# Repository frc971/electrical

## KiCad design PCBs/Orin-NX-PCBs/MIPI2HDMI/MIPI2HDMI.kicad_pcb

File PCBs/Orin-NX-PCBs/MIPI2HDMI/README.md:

Step file is made for mm and has .01mm accuracy.

Last Revision made on Nov 17 2023

For questions regarding the pcb or schematic contact Alex Lenkov or Scott Berman

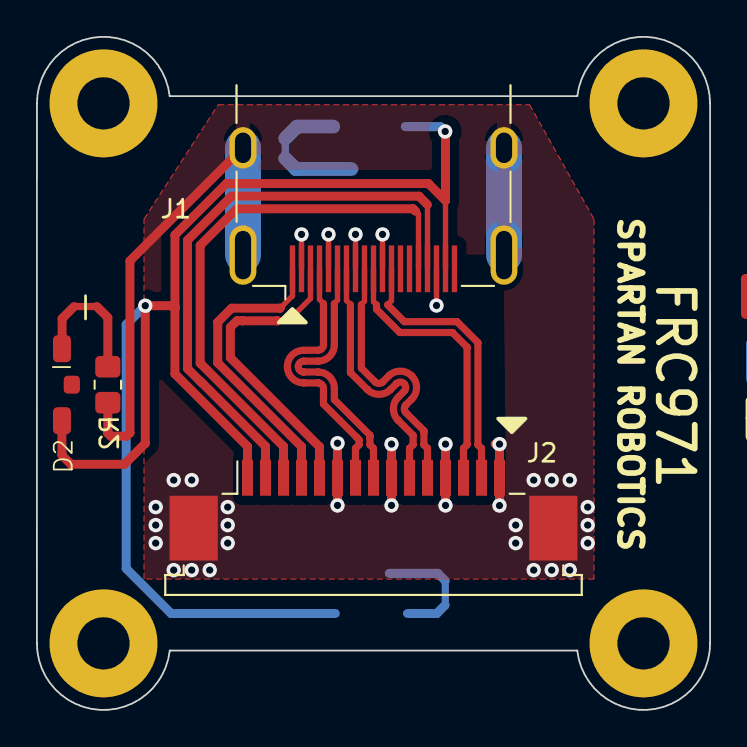
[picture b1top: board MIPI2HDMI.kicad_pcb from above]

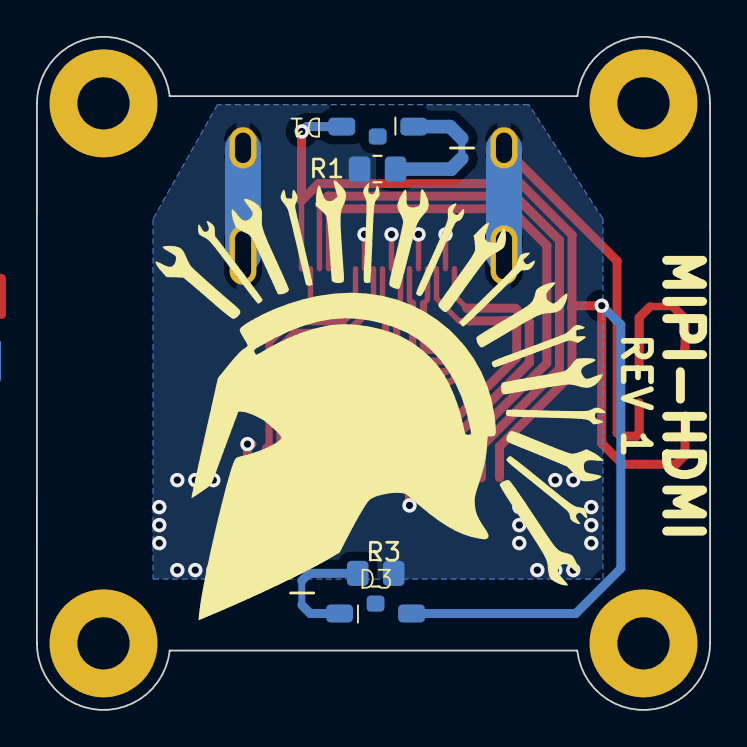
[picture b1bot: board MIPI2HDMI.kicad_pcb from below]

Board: 2 copper layers, 37.4 x 37.4 mm, 12 parts (4 on the bottom side), 15 nets.

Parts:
D1, D2, D3: LED; SM1204PGC
H1, H2, H3, H4: M2.5 Mounting Hole; MountingHole_2.7mm_Pad
J1: HDMI; HDMI_A_Molex_208658-1001_Horizontal
J2: 1-84953-5; TE_1-84953-5_1x15-1MP_P1.0mm_Horizontal
R1, R2, R3: 60; R_0805_2012Metric_Pad1.20x1.40mm_HandSolder

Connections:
+3V3: D1.1 (A), D2.1 (A), D3.1 (A), J1.18 (+5V), J2.15
/CAM_CK_N: J1.6 (D1-), J2.8
/CAM_CK_P: J1.4 (D1+), J2.9
/CAM_D0_N: J1.12 (CK-), J2.2
/CAM_D0_P: J1.10 (CK+), J2.3
/CAM_D1_N: J1.9 (D0-), J2.5
/CAM_D1_P: J1.7 (D0+), J2.6
/CAM_MCLK: J1.1 (D2+), J2.12
/CAM_SCL: J1.15 (SCL), J2.13
/CAM_SDA: J1.16 (SDA), J2.14
/PWR_DN_LS: J1.3 (D2-), J2.11
GND: J1.2 (D2S), J1.5 (D1S), J1.8 (D0S), J1.11 (CKS), J1.17 (GND), J1.SH, J2.1, J2.4, J2.7, J2.10, J2.16, J2.17, R1.2, R2.2, R3.2
unnamed: D1.2 (K), R1.1
unnamed: D2.2 (K), R2.1
unnamed: D3.2 (K), R3.1

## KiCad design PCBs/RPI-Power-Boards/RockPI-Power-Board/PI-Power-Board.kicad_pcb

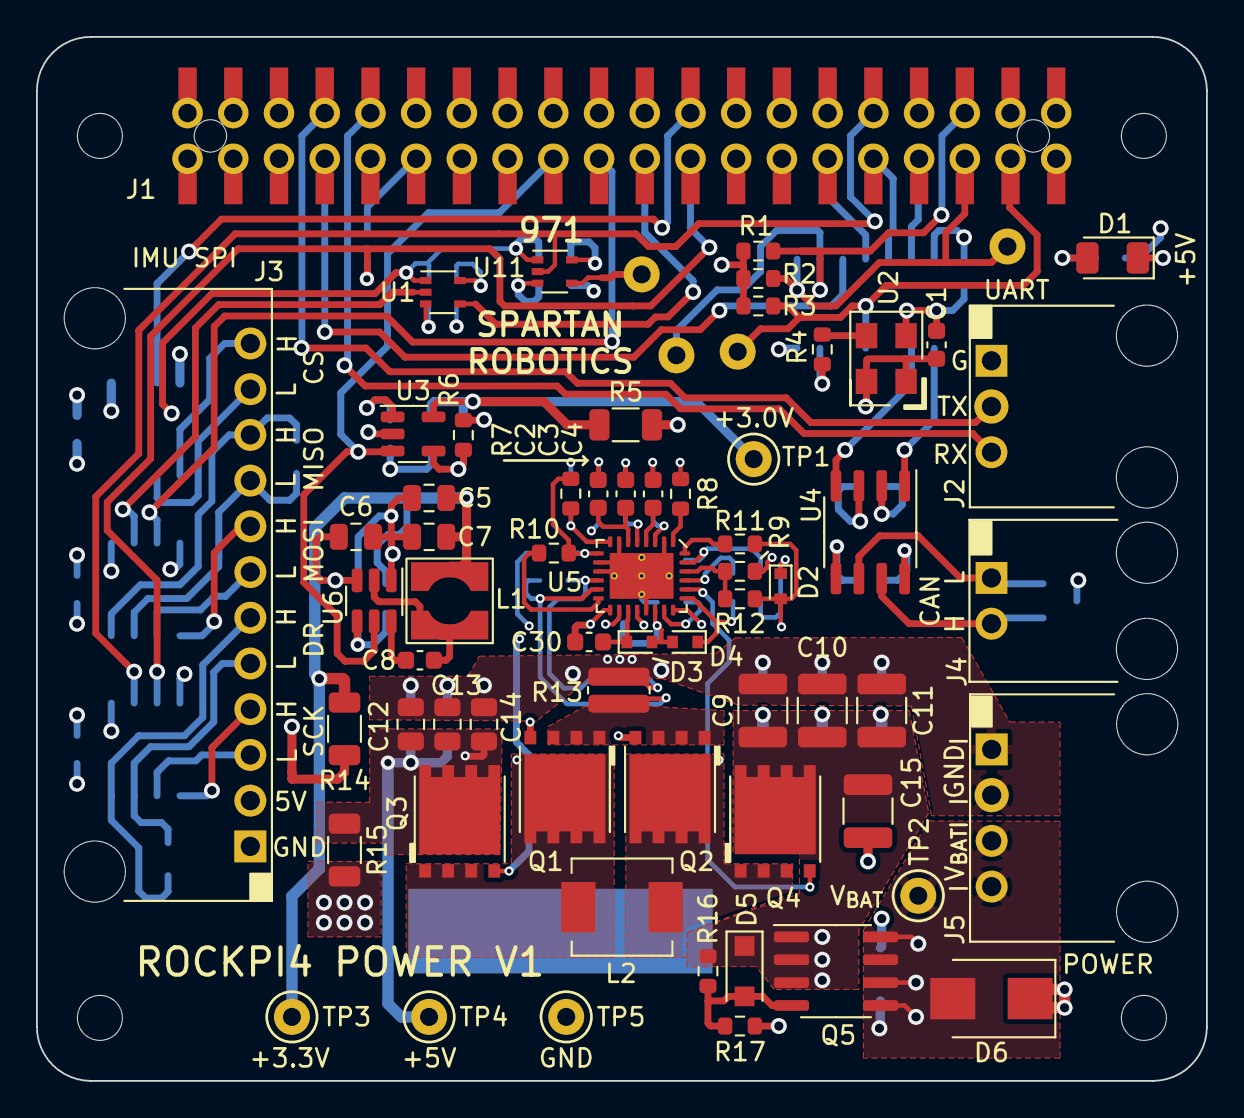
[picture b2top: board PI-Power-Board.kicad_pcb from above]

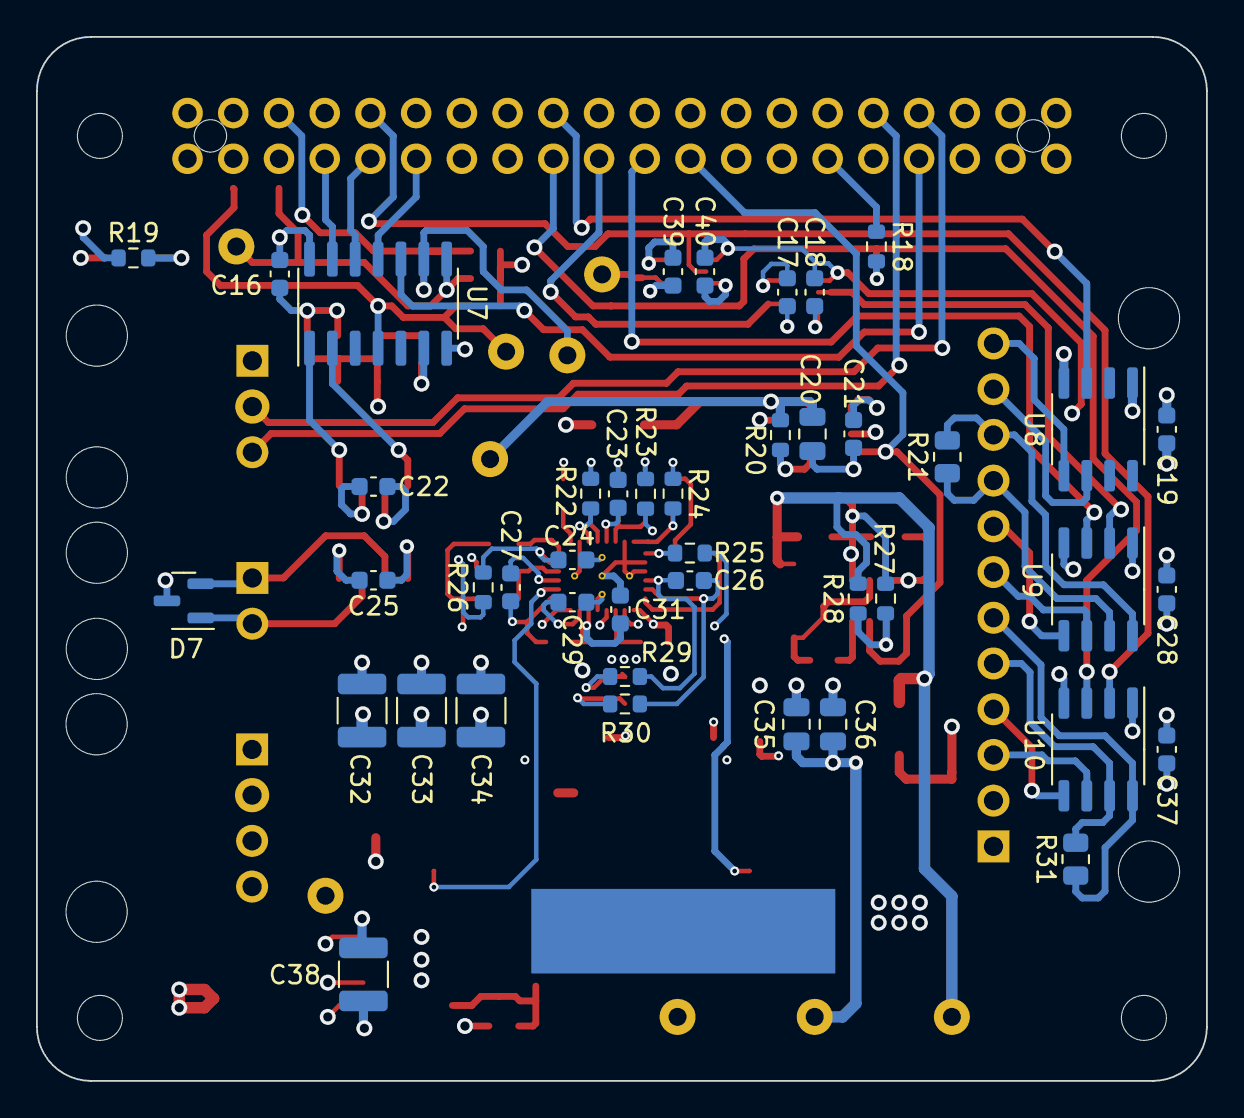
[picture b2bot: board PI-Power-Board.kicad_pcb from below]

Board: 4 copper layers, 65.0 x 58.0 mm, 118 parts (43 on the bottom side), 74 nets.

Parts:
C1, C8, C16, C17, C18, C19, C21, C22, C24, C25, C27, C28, C29, C30, C37, C39, C40: 0.1uF-10%-50V-0603; C_0603_1608Metric
C2, C23: 0.015uF-10%-50V-0603; C_0603_1608Metric
C3: 330pF-5%-50V-0603; C_0603_1608Metric
C4, C26: 47pF-5%-50V-0603; C_0603_1608Metric
C5, C6, C7, C12, C13, C14, C20, C35, C36: 22uF-10V-10%-0805; C_0805_2012Metric
C9, C10, C11, C15, C32, C33, C34, C38: 22uF-25V-10%-1210; C_1210_3225Metric
C31: 1.0uF-10%-10V-0603; C_0603_1608Metric
D1: +5V; LED_1206_3216Metric
D2, D3, D4: NSR05T40XV2T5G; D_SOD-523
D5: 15V; D_SOD-123F
D6: 15V; D_SMB
D7: PESD1CAN; SOT-23
H1, H3: Paste Slot 5x2.5mm; PASTE-SLOT-5x2.5mm
H2, H4, H6, H8: MTG Hole 2.5mm; MountingHole_2.5mm
H5, H7: Paste Hole 2.5mm; PASTE-HOLE-2.5mm
J1: PI Header; M20-782045
J2: UART; 70555-0002
J3: IMU SPI; 70555-0011
J4: CAN; 70555-0001
J5: POWER; 70555-0003
L1: 2.5uH-1.45A; WE-TPC-744031002
L2: 1.0 uH-13.7m-20%; IHLP2020CZER
Q1, Q2, Q3, Q4: CSD17577Q5A; TI-SON5x6
Q5: SI4483ADY-T1-GE3; SOIC-8_3.9x4.9mm_P1.27mm
R1, R2, R3, R9, R23: 2.00k-1%-0603; R_0603_1608Metric
R4: 49.9R-1%-0603; R_0603_1608Metric
R5, R14, R15: 0R-1206; R_1206_3216Metric
R6, R20: DNI-0603; R_0603_1608Metric
R7, R11: 105k-1%-0603; R_0603_1608Metric
R8: 93.1k-1%-0603; R_0603_1608Metric
R10: 10K0-1%-0603; R_0603_1608Metric
R12: 249k-1%-0603; R_0603_1608Metric
R13: 15m-1%-0612; R_0612_1632Metric
R16, R24: 20.0k-1%-0603; R_0603_1608Metric
R17, R19: 1.0k-1%-0603; R_0603_1608Metric
R18: 499R-1%-0603; R_0603_1608Metric
R21, R31: 120R-1%-0805; R_0805_2012Metric
R22: 15.8k-1%-0603; R_0603_1608Metric
R25: 0R-0603; R_0603_1608Metric
R26: 10R0-1%-0603; R_0603_1608Metric
R27: 31.6k-1%-0603; R_0603_1608Metric
R28: 10.0k-1%-0603; R_0603_1608Metric
R29, R30: 100R-1%-0603; R_0603_1608Metric
TP1: +3.0V; TestPoint_Keystone_5000-5004_Miniature
TP2: V_{BAT}; TestPoint_Keystone_5000-5004_Miniature
TP3, TP6, TP7, TP8, TP9: +3.3V; TestPoint_Keystone_5000-5004_Miniature
TP4: +5V; TestPoint_Keystone_5000-5004_Miniature
TP5: GND; TestPoint_Keystone_5000-5004_Miniature
U1, U11: NLSV1T34DFT2G; SOT-353_SC-70-5
U2: 40MHz; ECS-5032MV
U3: MIC5233-3.0YM5-TR; SOT-23-5
U4: MCP2542FD-E/SN; SO-8_3.9x4.9mm_P1.27mm
U5: LM5176RHF; QFN-28-1EP_4x5mm_P0.5mm_EP2.55x3.55mm_ThermalVias
U6: AP62200WU-7; TSOT-23-6
U7: MCP2517FDT-H/SL; SOIC-14_3.9x8.7mm_P1.27mm
U8, U9, U10: ADM3490ARZ; SO-8_3.9x4.9mm_P1.27mm

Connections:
+3V0: C1.1, C16.1, C17.1, C25.1, C39.1, R1.1, R2.1, R3.1, R5.2, U1.5 (VCCB), U2.1 (EN), U2.4 (V_{DD}), U4.5 (VIO), U7.14 (VDD), U11.5 (VCCB)
+3V3: C18.1, C19.1, C28.1, C37.1, C40.1, R14.2, U1.1 (VCCA), U8.1 (VCC), U9.1 (VCC), U10.1 (VCC), U11.1 (VCCA)
+5V: C6.1, C21.1, C22.1, J1.2, J1.4, J3.2, R15.2, R19.2, U3.1 (IN), U4.3 (VDD), U6.3 (VIN)
/3V3_PI: J1.17, U3.3 (EN), U6.5 (EN)
/3V-3.3V-PS/3V0_{OUT}: C20.1, R5.1, R20.1, TP1.1, U3.5 (OUT)
/3V-3.3V-PS/3V3_{OUT}: C5.1, C7.1, L1.2, R14.1, R27.1, TP3.1
/3V-3.3V-PS/SW: C8.2, L1.1, U6.2 (SW)
/5V PowerSupply/BIAS: C29.1, R25.1, U5.21 (BIAS)
/5V PowerSupply/BOOT_{1}: C27.1, D4.1 (K), U5.23 (BOOT1)
/5V PowerSupply/BOOT_{2}: C30.1, D3.1 (K), U5.17 (BOOT2)
/5V PowerSupply/COMP: C2.1, C3.1, U5.6 (COMP)
/5V PowerSupply/CS: C26.1, R30.1, U5.13 (CS)
/5V PowerSupply/CSG: C26.2, R29.1, U5.12 (CSG)
/5V PowerSupply/EN/UVLO: R11.1, R12.2, U5.26 (EN/UVLO)
/5V PowerSupply/FB: R7.2, R24.1, U5.8 (FB)
/5V PowerSupply/HDRV1: Q4.4 (G), U5.24 (HDRV1)
/5V PowerSupply/HDRV2: Q3.4 (G), U5.16 (HDRV2)
/5V PowerSupply/LDRV1: Q2.4 (G), U5.22 (LDRV1)
/5V PowerSupply/LDRV2: Q1.4 (G), U5.18 (LDRV2)
/5V PowerSupply/MODE: R8.1, U5.1 (MODE)
/5V PowerSupply/PGOOD: R10.2, U5.14 (PGOOD)
/5V PowerSupply/RT: R22.1, U5.3 (RT)
/5V PowerSupply/R_{CSP}: Q1.1 (S), Q1.2 (S), Q1.3 (S), Q2.1 (S), Q2.2 (S), Q2.3 (S), R13.1, R30.2
/5V PowerSupply/SLOPE: C4.1, U5.4 (SLOPE)
/5V PowerSupply/SS: C23.1, U5.5 (SS)
/5V PowerSupply/SW1: C27.2, L2.1, Q2.5 (D), Q4.1 (S), Q4.2 (S), Q4.3 (S), U5.25 (SW1)
/5V PowerSupply/SW2: C30.2, L2.2, Q1.5 (D), Q3.1 (S), Q3.2 (S), Q3.3 (S), U5.15 (SW2)
/5V PowerSupply/V_{CC}: C31.1, D3.2 (A), D4.2 (A), U5.20 (VCC)
/5V PowerSupply/V_{IN}: C24.1, R26.2, U5.27 (VIN)
/5V PowerSupply/V_{ISNS}: R9.2, U5.28 (VISNS)
/5V PowerSupply/V_{OSNS}: C12.1, C13.1, C14.1, C35.1, C36.1, Q3.5 (D), R7.1, R10.1, R15.1, R25.2, TP4.1, U5.9 (VOSNS)
/5V PowerSupply/V_{P}: C9.2, C10.2, C11.2, C15.2, C32.2, C33.2, C34.2, D2.2 (A), D5.1 (K), Q4.5 (D), Q5.1 (S), Q5.2 (S), Q5.3 (S), R9.1, R12.1, R16.2
/CAN-FD/CAN_H: D7.1 (K1), J4.2, U4.7 (CANH)
/CAN-FD/CAN_L: D7.2 (K1), J4.1, U4.6 (CANL)
/CS_H: J3.12, U8.5
/CS_L: J3.11, U8.6
/DR: J1.32, U10.2 (RO), U11.2 (A)
/DR_H: J3.6, R31.1, U10.8
/DR_L: J3.5, R31.2, U10.7
/MISO_H: J3.10, R21.1, U9.8
/MISO_L: J3.9, R21.2, U9.7
/MOSI_H: J3.8, U9.5
/MOSI_L: J3.7, U9.6
/PWM0: J1.11, R18.1
/SCK_H: J3.4, U10.5
/SCK_L: J3.3, U10.6
/SPI1_CLK: J1.23, R18.2, U10.3 (DI)
/SPI1_RXD: J1.21, U1.4 (B)
/SPI1_TXD: J1.19, U9.3 (DI)
/SPI2_CLK: J1.7, U7.10 (SCK)
/SPI2_RXD: J1.31, U7.12 (SDO)
/SPI2_TXD: J1.29, U7.11 (SDI)
/UART2_RXD: J1.10, J2.3
/UART2_TXD: J1.8, J2.2
/VBAT: C38.2, D6.2 (A2), J5.3, J5.4, Q5.5 (D), Q5.6 (D), Q5.7 (D), Q5.8 (D), TP2.1
/~CAN_INT0: J1.37, R3.2, TP6.1, U7.4 (~INT)
/~CAN_INT1: J1.36, R1.2, TP7.1, U7.9 (~INT0/GPIO0/XSTBY)
/~CAN_INT: J1.35, R2.2, TP8.1, U7.8 (~INT1/GPIO1)
/~SPI1_CS: J1.24, U8.3 (DI)
/~SPI2_CS: J1.33, U7.13 (nCS)
GND: C1.2, C3.2, C4.2, C5.2, C6.2, C7.2, C9.1, C10.1, C11.1, C12.2, C13.2, C14.2, C15.1, C16.2, C17.2, C18.2, C19.2, C20.2, C21.2, C22.2, C23.2, C24.2, C25.2, C28.2, C29.2, C31.2, C32.1, C33.1, C34.1, C35.2, C36.2, C37.2, C38.1, C39.2, C40.2, D1.1 (K), D6.1 (A1), D7.3 (KK), J1.6, J1.9, J1.14, J1.20, J1.25, J1.30, J1.34, J1.39, J2.1, J3.1, J5.1, J5.2, R6.2, R8.2, R11.2, R13.2, R17.1, R22.2, R23.2, R24.2, R28.2, R29.2, TP5.1, U1.3 (GND), U2.2 (GND), U3.2 (GND), U4.2 (VSS), U4.8 (STBY), U5.2 (DITH), U5.7 (AGND), U5.10 (ISNS-), U5.11 (ISNS+), U5.19 (PGND), U5.29 (EP-PGND), U6.1 (GND), U7.7 (VSS), U8.4 (GND), U9.4 (GND), U10.4 (GND), U11.3 (GND)
unnamed: C2.2, R23.1
unnamed: C8.1, U6.6 (BST)
unnamed: D1.2 (A), R19.1
unnamed: D2.1 (K), R26.1
unnamed: D5.2 (A), Q5.4 (G), R16.1, R17.2
unnamed: R4.1, U2.3 (OUT)
unnamed: R4.2, U7.6 (OSC1)
unnamed: R6.1, R20.2, U3.4 (NC/ADJ)
unnamed: R27.2, R28.1, U6.4 (FB)
unnamed: TP9.1, U11.4 (B)
unnamed: U1.2 (A), U9.2 (RO)
unnamed: U4.1 (TXD), U7.1 (TXCAN)
unnamed: U4.4 (RXD), U7.2 (RXCAN)

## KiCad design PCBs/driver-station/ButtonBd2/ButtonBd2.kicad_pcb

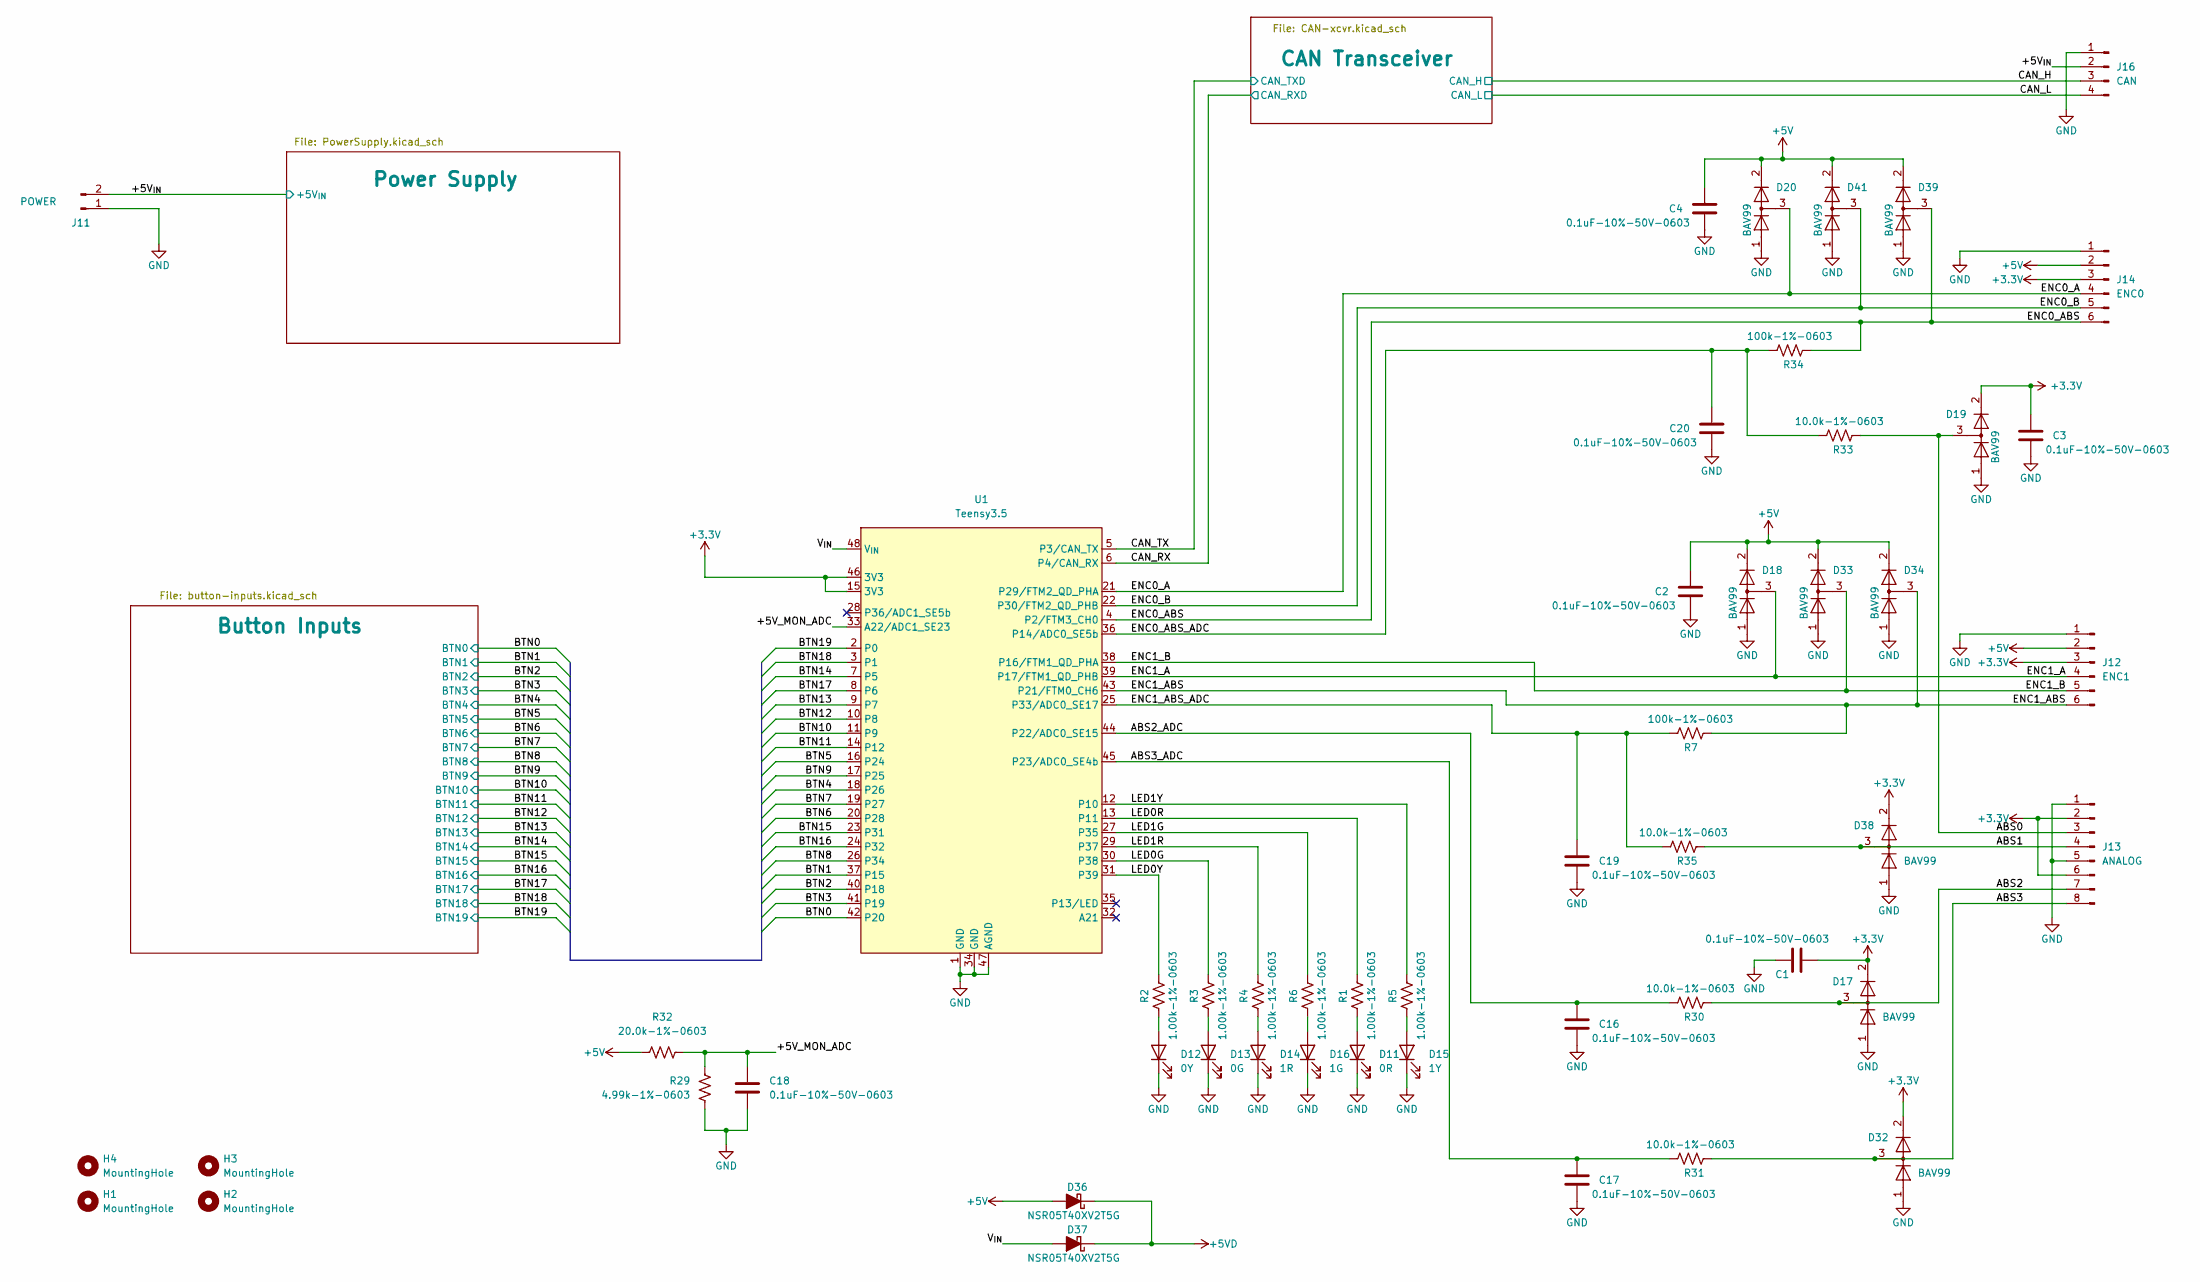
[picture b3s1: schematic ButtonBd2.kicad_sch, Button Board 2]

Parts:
C1, C2, C3, C4, C16, C17, C18, C19, C20: 0.1uF-10%-50V-0603; C_0603_1608Metric; MFG P/N CL10B104KB8NNNC
D11: 0R; LED_0603_1608Metric; MFG P/N BR1111C-TR
D12: 0Y; LED_0603_1608Metric; MFG P/N 150060YS75000
D13: 0G; LED_0603_1608Metric; MFG P/N 150060GS75000
D14: 1R; LED_0603_1608Metric; MFG P/N BR1111C-TR
D15: 1Y; LED_0603_1608Metric; MFG P/N 150060YS75000
D16: 1G; LED_0603_1608Metric; MFG P/N 150060GS75000
D17, D18, D19, D20, D32, D33, D34, D38, D39, D41: BAV99; SOT-23; MFG P/N BAV99,235
D36, D37: NSR05T40XV2T5G; D_SOD-523; MFG P/N NSR05T40XV2T5G
H1, H2, H3, H4: MountingHole; MountingHole_3.2mm_M3
J11: POWER; 70543-0001; MFG P/N 70541-0001
J12: ENC1; 70543-0005; MFG P/N 70541-0005
J13: ANALOG; 70543-0007; MFG P/N 70541-0007
J14: ENC0; 70543-0005; MFG P/N 70541-0005
J16: CAN; 70543-0003; MFG P/N 70541-0003
R1, R2, R3, R4, R5, R6: 1.00k-1%-0603; R_0603_1608Metric; MFG P/N RNCP0603FTD1K00
R7, R34: 100k-1%-0603; R_0603_1608Metric; MFG P/N RC0603FR-07100KL
R29: 4.99k-1%-0603; R_0603_1608Metric; MFG P/N RMCF0603FT4R99
R30, R31, R33, R35: 10.0k-1%-0603; R_0603_1608Metric; MFG P/N RC0603FR-0710KL
R32: 20.0k-1%-0603; R_0603_1608Metric; MFG P/N RC0603FR-0720KL
U1: Teensy3.5; Teensy-DIP-49_W15.24mm_Socket; MFG P/N TEENSY 3.5

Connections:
+3.3V: C1.2, C3.1, D17.2 (A), D19.2 (A), D32.2 (A), D38.2 (A), J12.3, J13.2, J13.6, J14.3, U1.15 (3V3), U1.46 (3V3); also elsewhere on the board
+5V: C2.1, C4.1, D18.2 (A), D20.2 (A), D33.2 (A), D34.2 (A), D36.2 (A), D39.2 (A), D41.2 (A), J12.2, J14.2, R32.2; also elsewhere on the board
+5VD: D36.1 (K), D37.1 (K); also elsewhere on the board
/+5V_MON_ADC: C18.1, R29.1, R32.1, U1.33 (A22/ADC1_SE23)
/+5V_{IN}: J11.2, J16.2; also elsewhere on the board
/ABS0: D19.3 (K), J13.3, R33.2
/ABS1: D38.3 (K), J13.4, R35.2
/ABS2: D17.3 (K), J13.7, R30.2
/ABS2_ADC: C16.1, R30.1, U1.44 (P22/ADC0_SE15)
/ABS3: D32.3 (K), J13.8, R31.2
/ABS3_ADC: C17.1, R31.1, U1.45 (P23/ADC0_SE4b)
/BTN0: U1.42 (P20); also elsewhere on the board
/BTN1: U1.37 (P15); also elsewhere on the board
/BTN2: U1.40 (P18); also elsewhere on the board
/BTN3: U1.41 (P19); also elsewhere on the board
/BTN4: U1.18 (P26); also elsewhere on the board
/BTN5: U1.16 (P24); also elsewhere on the board
/BTN6: U1.20 (P28); also elsewhere on the board
/BTN7: U1.19 (P27); also elsewhere on the board
/BTN8: U1.26 (P34); also elsewhere on the board
/BTN9: U1.17 (P25); also elsewhere on the board
/BTN10: U1.11 (P9); also elsewhere on the board
/BTN11: U1.14 (P12); also elsewhere on the board
/BTN12: U1.10 (P8); also elsewhere on the board
/BTN13: U1.9 (P7); also elsewhere on the board
/BTN14: U1.7 (P5); also elsewhere on the board
/BTN15: U1.23 (P31); also elsewhere on the board
/BTN16: U1.24 (P32); also elsewhere on the board
/BTN17: U1.8 (P6); also elsewhere on the board
/BTN18: U1.3 (P1); also elsewhere on the board
/BTN19: U1.2 (P0); also elsewhere on the board
/CAN_H: J16.3; also elsewhere on the board
/CAN_L: J16.4; also elsewhere on the board
/CAN_RX: U1.6 (P4/CAN_RX); also elsewhere on the board
/CAN_TX: U1.5 (P3/CAN_TX); also elsewhere on the board
/ENC0_A: D20.3 (K), J14.4, U1.21 (P29/FTM2_QD_PHA)
/ENC0_ABS: D39.3 (K), J14.6, R34.2, U1.4 (P2/FTM3_CH0)
/ENC0_ABS_ADC: C20.1, R33.1, R34.1, U1.36 (P14/ADC0_SE5b)
/ENC0_B: D41.3 (K), J14.5, U1.22 (P30/FTM2_QD_PHB)
/ENC1_A: D18.3 (K), J12.4, U1.39 (P17/FTM1_QD_PHB)
/ENC1_ABS: D34.3 (K), J12.6, R7.2, U1.43 (P21/FTM0_CH6)
/ENC1_ABS_ADC: C19.1, R7.1, R35.1, U1.25 (P33/ADC0_SE17)
/ENC1_B: D33.3 (K), J12.5, U1.38 (P16/FTM1_QD_PHA)
/LED0G: R3.1, U1.30 (P38)
/LED0R: R1.1, U1.13 (P11)
/LED0Y: R2.1, U1.31 (P39)
/LED1G: R6.1, U1.27 (P35)
/LED1R: R4.1, U1.29 (P37)
/LED1Y: R5.1, U1.12 (P10)
/V_{IN}: D37.2 (A), U1.48 (V_{IN})
GND: C1.1, C2.2, C3.2, C4.2, C16.2, C17.2, C18.2, C19.2, C20.2, D11.1 (K), D12.1 (K), D13.1 (K), D14.1 (K), D15.1 (K), D16.1 (K), D17.1 (K), D18.1 (K), D19.1 (K), D20.1 (K), D32.1 (K), D33.1 (K), D34.1 (K), D38.1 (K), D39.1 (K), D41.1 (K), J11.1, J12.1, J13.1, J13.5, J14.1, J16.1, R29.2, U1.1 (GND), U1.34 (GND), U1.47 (AGND); also elsewhere on the board
unnamed: D11.2 (A), R1.2
unnamed: D12.2 (A), R2.2
unnamed: D13.2 (A), R3.2
unnamed: D14.2 (A), R4.2
unnamed: D15.2 (A), R5.2
unnamed: D16.2 (A), R6.2

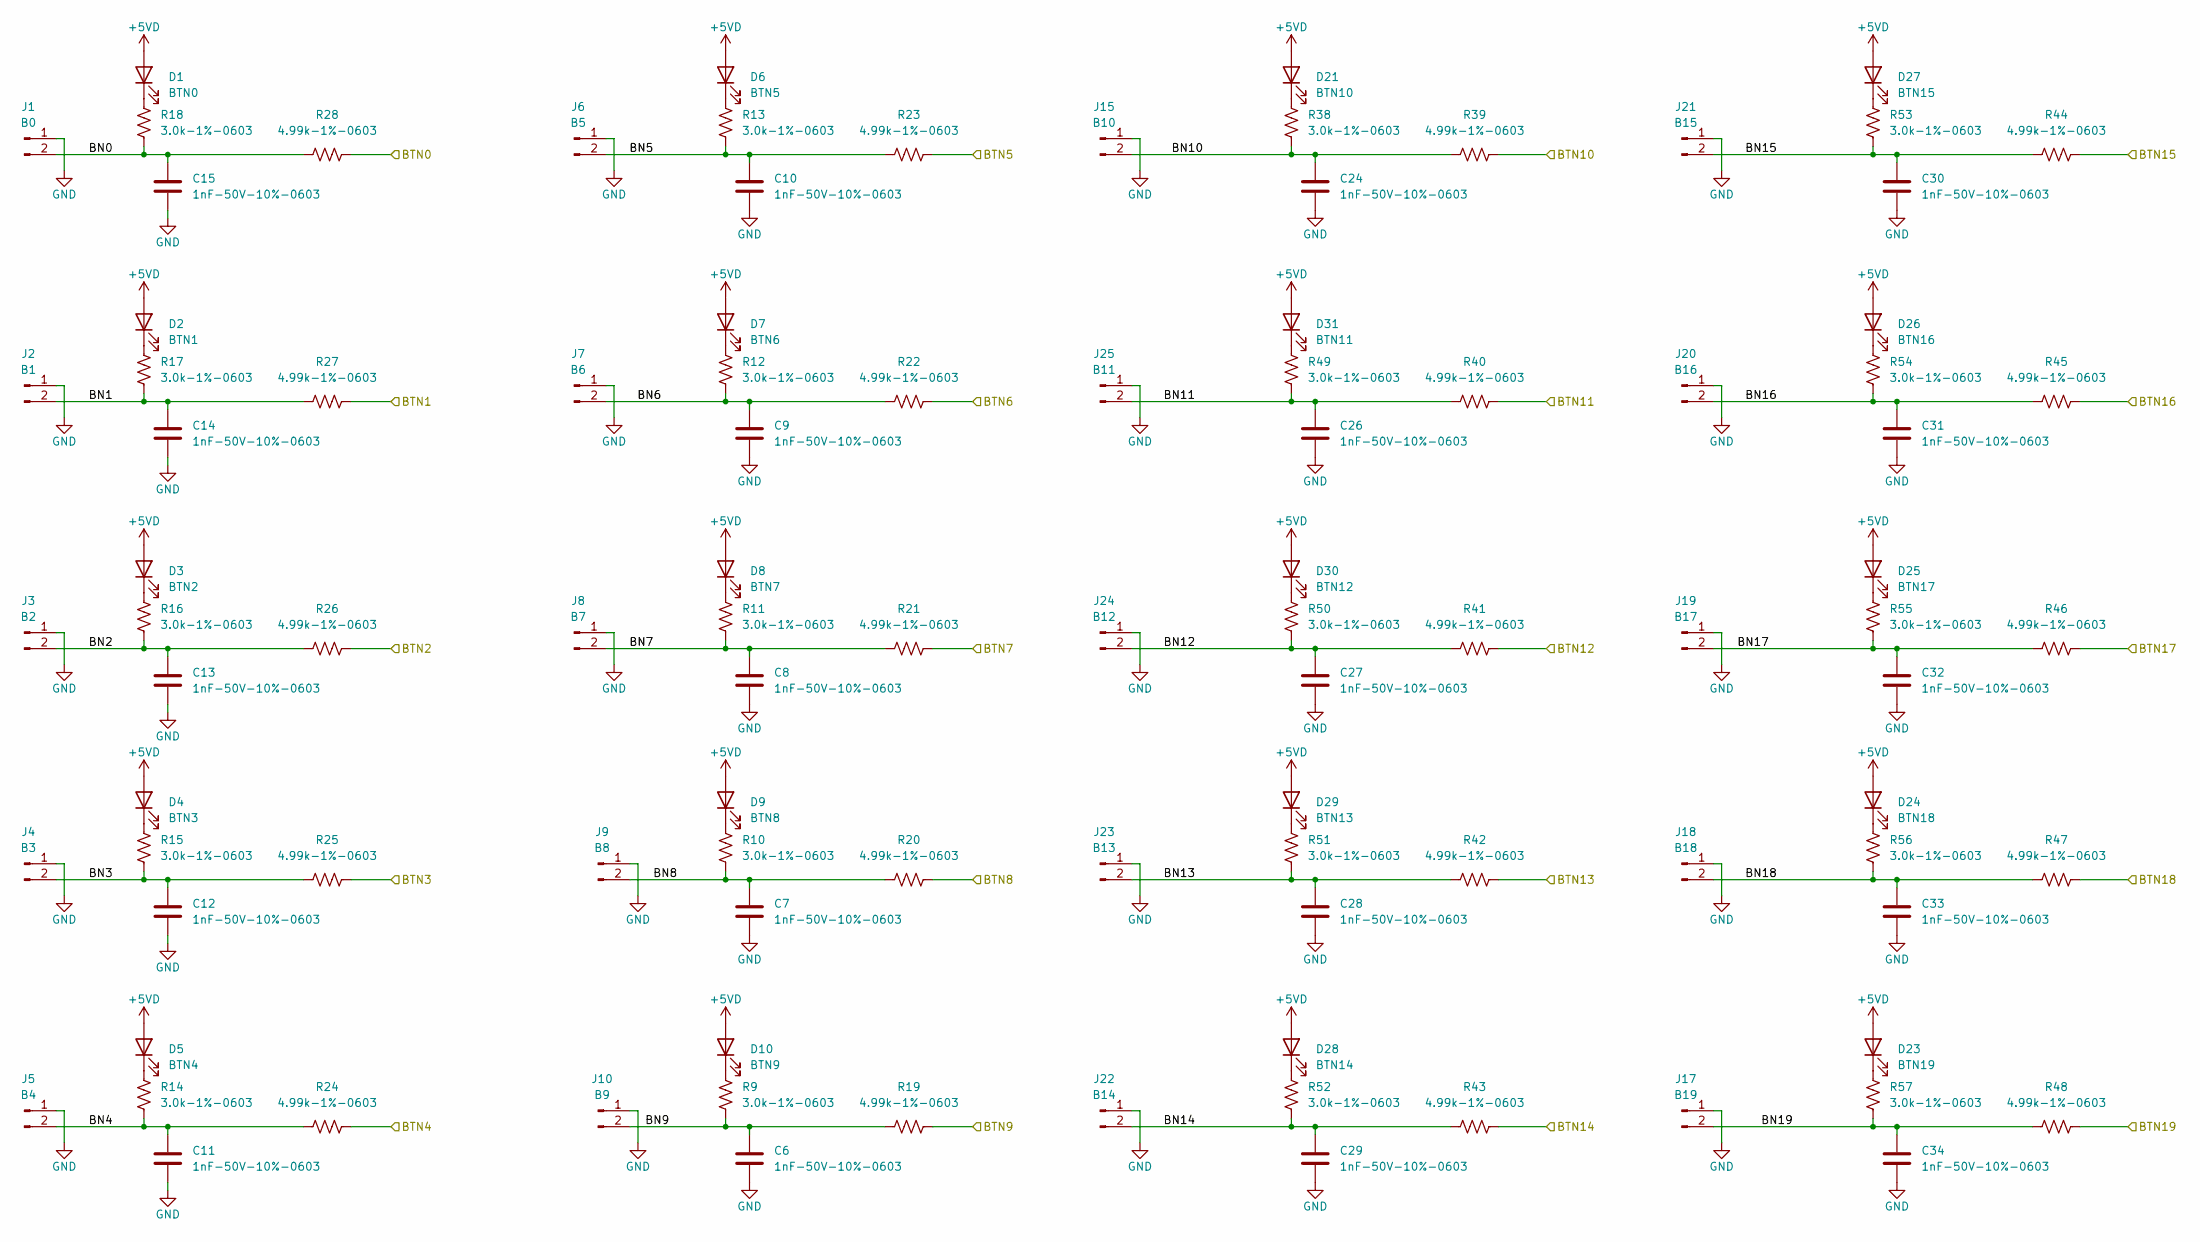
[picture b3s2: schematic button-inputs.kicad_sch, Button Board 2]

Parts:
C6, C7, C8, C9, C10, C11, C12, C13, C14, C15, C24, C26, C27, C28, C29, C30, C31, C32, C33, C34: 1nF-50V-10%-0603; C_0603_1608Metric; MFG P/N CL10B102KB8NNNC
D1: BTN0; LED_0603_1608Metric; MFG P/N 150060YS75000
D2: BTN1; LED_0603_1608Metric; MFG P/N 150060YS75000
D3: BTN2; LED_0603_1608Metric; MFG P/N 150060YS75000
D4: BTN3; LED_0603_1608Metric; MFG P/N 150060YS75000
D5: BTN4; LED_0603_1608Metric; MFG P/N 150060YS75000
D6: BTN5; LED_0603_1608Metric; MFG P/N 150060YS75000
D7: BTN6; LED_0603_1608Metric; MFG P/N 150060YS75000
D8: BTN7; LED_0603_1608Metric; MFG P/N 150060YS75000
D9: BTN8; LED_0603_1608Metric; MFG P/N 150060YS75000
D10: BTN9; LED_0603_1608Metric; MFG P/N 150060YS75000
D21: BTN10; LED_0603_1608Metric; MFG P/N 150060YS75000
D23: BTN19; LED_0603_1608Metric; MFG P/N 150060YS75000
D24: BTN18; LED_0603_1608Metric; MFG P/N 150060YS75000
D25: BTN17; LED_0603_1608Metric; MFG P/N 150060YS75000
D26: BTN16; LED_0603_1608Metric; MFG P/N 150060YS75000
D27: BTN15; LED_0603_1608Metric; MFG P/N 150060YS75000
D28: BTN14; LED_0603_1608Metric; MFG P/N 150060YS75000
D29: BTN13; LED_0603_1608Metric; MFG P/N 150060YS75000
D30: BTN12; LED_0603_1608Metric; MFG P/N 150060YS75000
D31: BTN11; LED_0603_1608Metric; MFG P/N 150060YS75000
J1: B0; 70543-0001; MFG P/N 70541-0001
J2: B1; 70543-0001; MFG P/N 70541-0001
J3: B2; 70543-0001; MFG P/N 70541-0001
J4: B3; 70543-0001; MFG P/N 70541-0001
J5: B4; 70543-0001; MFG P/N 70541-0001
J6: B5; 70543-0001; MFG P/N 70541-0001
J7: B6; 70543-0001; MFG P/N 70541-0001
J8: B7; 70543-0001; MFG P/N 70541-0001
J9: B8; 70543-0001; MFG P/N 70541-0001
J10: B9; 70543-0001; MFG P/N 70541-0001
J15: B10; 70543-0001; MFG P/N 70541-0001
J17: B19; 70543-0001; MFG P/N 70541-0001
J18: B18; 70543-0001; MFG P/N 70541-0001
J19: B17; 70543-0001; MFG P/N 70541-0001
J20: B16; 70543-0001; MFG P/N 70541-0001
J21: B15; 70543-0001; MFG P/N 70541-0001
J22: B14; 70543-0001; MFG P/N 70541-0001
J23: B13; 70543-0001; MFG P/N 70541-0001
J24: B12; 70543-0001; MFG P/N 70541-0001
J25: B11; 70543-0001; MFG P/N 70541-0001
R9, R10, R11, R12, R13, R14, R15, R16, R17, R18, R38, R49, R50, R51, R52, R53, R54, R55, R56, R57: 3.0k-1%-0603; R_0603_1608Metric; MFG P/N RC0603FR-073KL
R19, R20, R21, R22, R23, R24, R25, R26, R27, R28, R39, R40, R41, R42, R43, R44, R45, R46, R47, R48: 4.99k-1%-0603; R_0603_1608Metric; MFG P/N RMCF0603FT4R99

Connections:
+5VD: D1.2 (A), D2.2 (A), D3.2 (A), D4.2 (A), D5.2 (A), D6.2 (A), D7.2 (A), D8.2 (A), D9.2 (A), D10.2 (A), D21.2 (A), D23.2 (A), D24.2 (A), D25.2 (A), D26.2 (A), D27.2 (A), D28.2 (A), D29.2 (A), D30.2 (A), D31.2 (A); also elsewhere on the board
/BTN0: R28.2; also elsewhere on the board
/BTN1: R27.2; also elsewhere on the board
/BTN2: R26.2; also elsewhere on the board
/BTN3: R25.2; also elsewhere on the board
/BTN4: R24.2; also elsewhere on the board
/BTN5: R23.2; also elsewhere on the board
/BTN6: R22.2; also elsewhere on the board
/BTN7: R21.2; also elsewhere on the board
/BTN8: R20.2; also elsewhere on the board
/BTN9: R19.2; also elsewhere on the board
/BTN10: R39.2; also elsewhere on the board
/BTN11: R40.2; also elsewhere on the board
/BTN12: R41.2; also elsewhere on the board
/BTN13: R42.2; also elsewhere on the board
/BTN14: R43.2; also elsewhere on the board
/BTN15: R44.2; also elsewhere on the board
/BTN16: R45.2; also elsewhere on the board
/BTN17: R46.2; also elsewhere on the board
/BTN18: R47.2; also elsewhere on the board
/BTN19: R48.2; also elsewhere on the board
/Button Inputs/BN0: C15.1, J1.2, R18.2, R28.1
/Button Inputs/BN1: C14.1, J2.2, R17.2, R27.1
/Button Inputs/BN2: C13.1, J3.2, R16.2, R26.1
/Button Inputs/BN3: C12.1, J4.2, R15.2, R25.1
/Button Inputs/BN4: C11.1, J5.2, R14.2, R24.1
/Button Inputs/BN5: C10.1, J6.2, R13.2, R23.1
/Button Inputs/BN6: C9.1, J7.2, R12.2, R22.1
/Button Inputs/BN7: C8.1, J8.2, R11.2, R21.1
/Button Inputs/BN8: C7.1, J9.2, R10.2, R20.1
/Button Inputs/BN9: C6.1, J10.2, R9.2, R19.1
/Button Inputs/BN10: C24.1, J15.2, R38.2, R39.1
/Button Inputs/BN11: C26.1, J25.2, R40.1, R49.2
/Button Inputs/BN12: C27.1, J24.2, R41.1, R50.2
/Button Inputs/BN13: C28.1, J23.2, R42.1, R51.2
/Button Inputs/BN14: C29.1, J22.2, R43.1, R52.2
/Button Inputs/BN15: C30.1, J21.2, R44.1, R53.2
/Button Inputs/BN16: C31.1, J20.2, R45.1, R54.2
/Button Inputs/BN17: C32.1, J19.2, R46.1, R55.2
/Button Inputs/BN18: C33.1, J18.2, R47.1, R56.2
/Button Inputs/BN19: C34.1, J17.2, R48.1, R57.2; also elsewhere on the board
GND: C6.2, C7.2, C8.2, C9.2, C10.2, C11.2, C12.2, C13.2, C14.2, C15.2, C24.2, C26.2, C27.2, C28.2, C29.2, C30.2, C31.2, C32.2, C33.2, C34.2, J1.1, J2.1, J3.1, J4.1, J5.1, J6.1, J7.1, J8.1, J9.1, J10.1, J15.1, J17.1, J18.1, J19.1, J20.1, J21.1, J22.1, J23.1, J24.1, J25.1; also elsewhere on the board
unnamed: D1.1 (K), R18.1
unnamed: D2.1 (K), R17.1
unnamed: D3.1 (K), R16.1
unnamed: D4.1 (K), R15.1
unnamed: D5.1 (K), R14.1
unnamed: D6.1 (K), R13.1
unnamed: D7.1 (K), R12.1
unnamed: D8.1 (K), R11.1
unnamed: D9.1 (K), R10.1
unnamed: D10.1 (K), R9.1
unnamed: D21.1 (K), R38.1
unnamed: D23.1 (K), R57.1
unnamed: D24.1 (K), R56.1
unnamed: D25.1 (K), R55.1
unnamed: D26.1 (K), R54.1
unnamed: D27.1 (K), R53.1
unnamed: D28.1 (K), R52.1
unnamed: D29.1 (K), R51.1
unnamed: D30.1 (K), R50.1
unnamed: D31.1 (K), R49.1

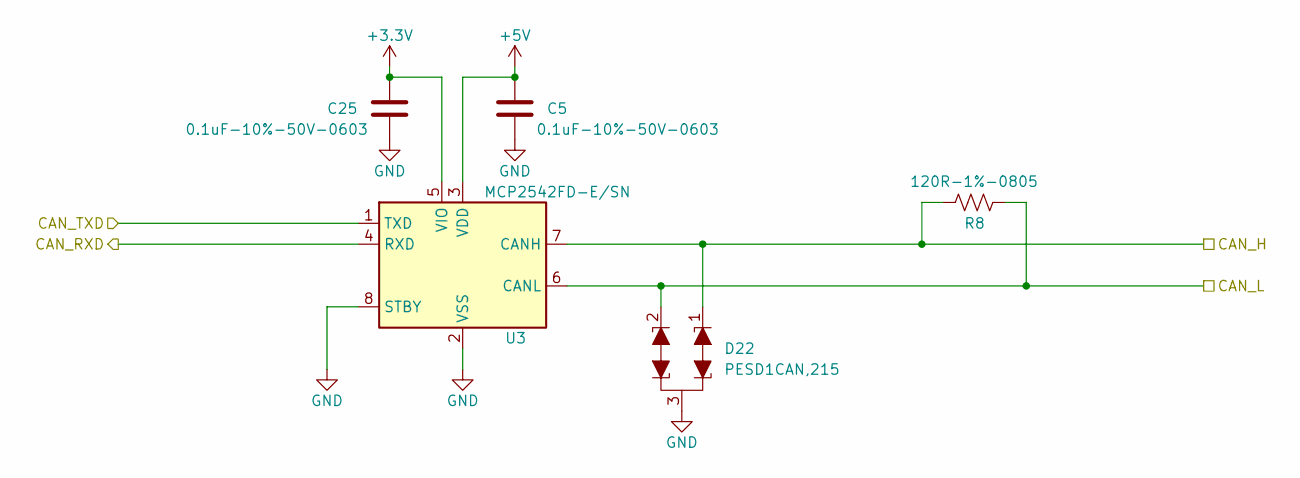
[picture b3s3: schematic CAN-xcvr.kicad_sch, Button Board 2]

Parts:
C5, C25: 0.1uF-10%-50V-0603; C_0603_1608Metric; MFG P/N CL10B104KB8NNNC
D22: PESD1CAN; SOT-23; MFG P/N PESD1CAN,215
R8: 120R-1%-0805; R_0805_2012Metric; MFG P/N RMCF0805FT120R
U3: MCP2542FD-E/SN; SO-8_3.9x4.9mm_P1.27mm; MFG P/N MCP2542FD-E/SN

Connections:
+3.3V: C25.1, U3.5 (VIO); also elsewhere on the board
+5V: C5.1, U3.3 (VDD); also elsewhere on the board
/CAN_H: D22.1 (K1), R8.1, U3.7 (CANH); also elsewhere on the board
/CAN_L: D22.2 (K1), R8.2, U3.6 (CANL); also elsewhere on the board
/CAN_RX: U3.4 (RXD); also elsewhere on the board
/CAN_TX: U3.1 (TXD); also elsewhere on the board
GND: C5.2, C25.2, D22.3 (KK), U3.2 (VSS), U3.8 (STBY); also elsewhere on the board

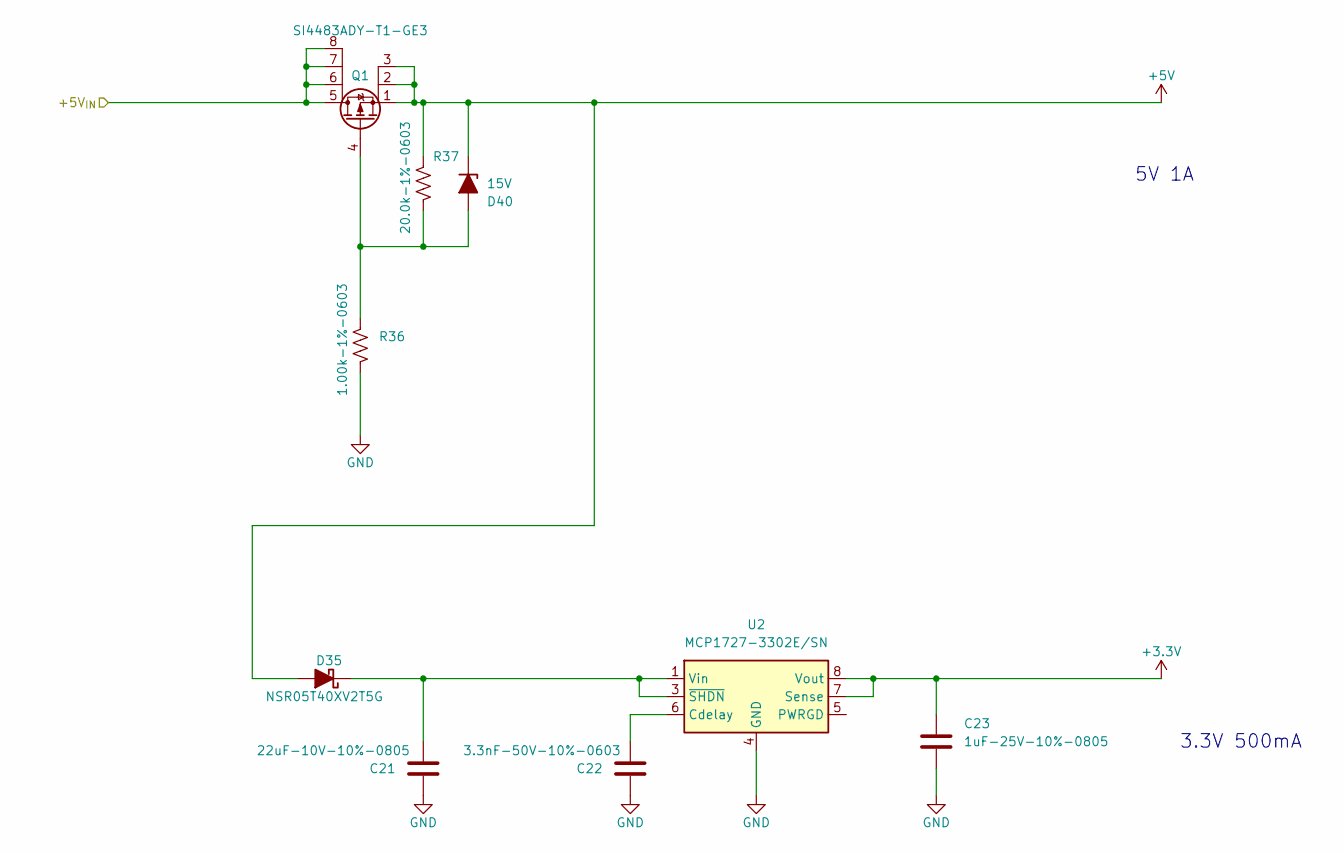
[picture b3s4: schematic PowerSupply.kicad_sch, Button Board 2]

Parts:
C21: 22uF-10V-10%-0805; C_0805_2012Metric; MFG P/N CL21A226KPCLRNC
C22: 3.3nF-50V-10%-0603; C_0603_1608Metric; MFG P/N CL10B332KB8NNNC
C23: 1uF-25V-10%-0805; C_0805_2012Metric; MFG P/N CL21B105KAFNNNE
D35: NSR05T40XV2T5G; D_SOD-523; MFG P/N NSR05T40XV2T5G
D40: 15V; D_SOD-123F; MFG P/N BZT52H-C15,115
Q1: SI4483ADY-T1-GE3; SOIC-8_3.9x4.9mm_P1.27mm; MFG P/N SI4483ADY-T1-GE3
R36: 1.00k-1%-0603; R_0603_1608Metric; MFG P/N RNCP0603FTD1K00
R37: 20.0k-1%-0603; R_0603_1608Metric; MFG P/N RC0603FR-0720KL
U2: MCP1727-3302E/SN; SOIC-8_3.9x4.9mm_P1.27mm; MFG P/N MCP1727-3302E/SN

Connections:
+3.3V: C23.1, U2.7 (Sense), U2.8 (Vout); also elsewhere on the board
+5V: D35.2 (A), D40.1 (K), Q1.1 (S), Q1.2 (S), Q1.3 (S), R37.2; also elsewhere on the board
/+5V_{IN}: Q1.5 (D), Q1.6 (D), Q1.7 (D), Q1.8 (D); also elsewhere on the board
GND: C21.2, C22.2, C23.2, R36.1, U2.4 (GND); also elsewhere on the board
unnamed: C21.1, D35.1 (K), U2.1 (Vin), U2.2 (Vin), U2.3 (~SHDN)
unnamed: C22.1, U2.6 (Cdelay)
unnamed: D40.2 (A), Q1.4 (G), R36.2, R37.1

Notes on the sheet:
3.3V 500mA
5V 1A

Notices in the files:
parts and their libraries:
Copyright 2021 Accelerated Designs. All rights reserved.
